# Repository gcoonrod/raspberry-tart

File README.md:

# raspberry-tart

 Raspberry Pi Pico Debug Hat for Pi 3/4

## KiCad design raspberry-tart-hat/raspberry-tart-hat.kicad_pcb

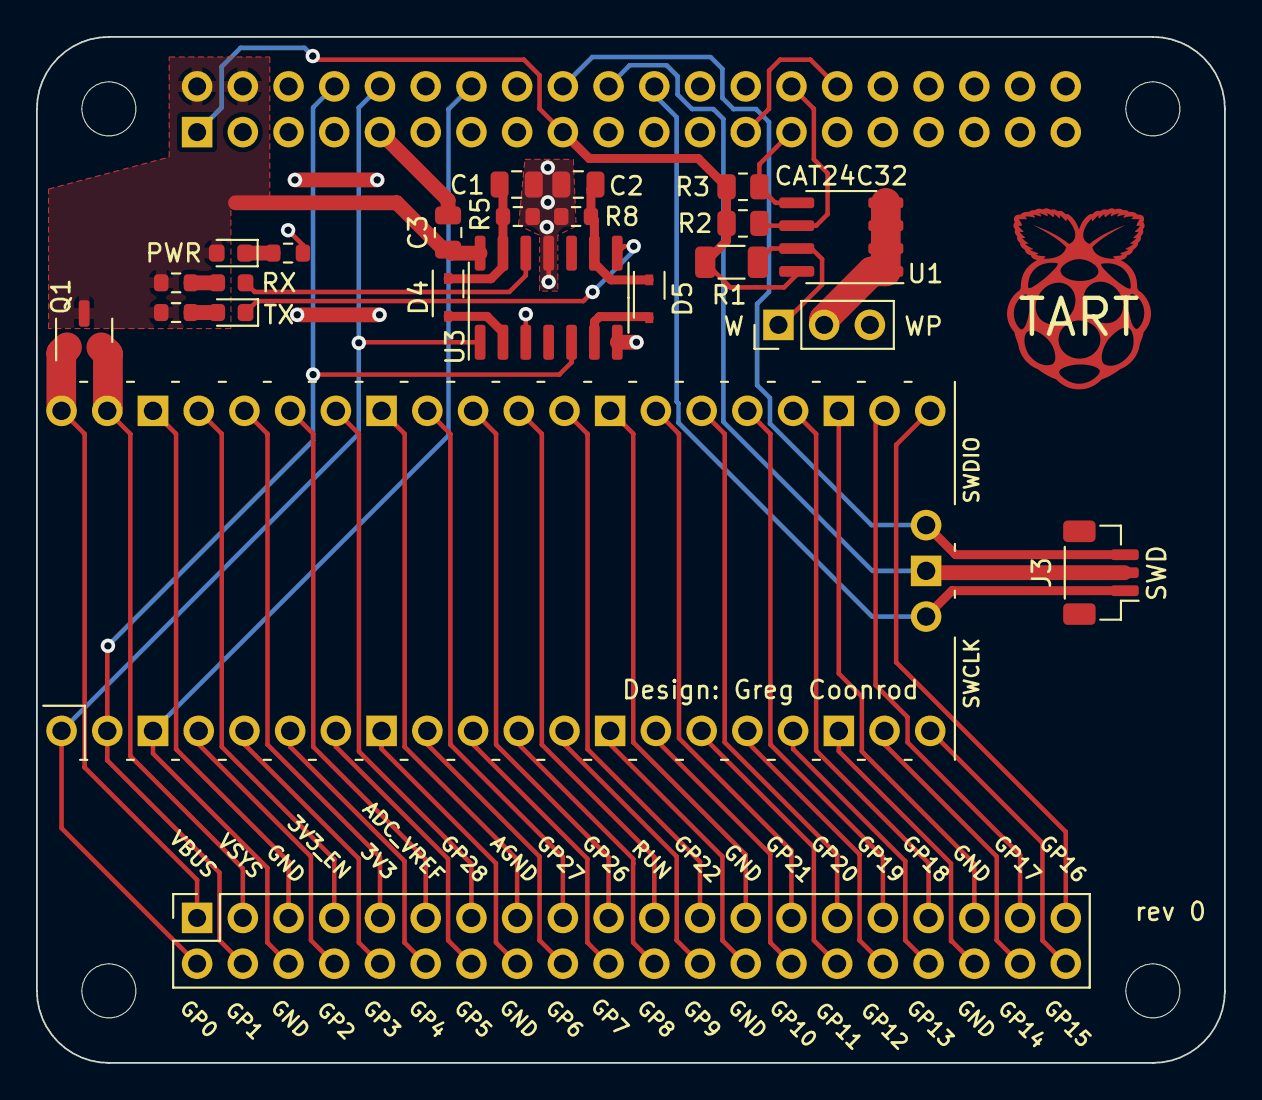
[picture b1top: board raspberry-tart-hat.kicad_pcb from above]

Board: 2 copper layers, 66.0 x 57.0 mm, 28 parts (1 on the bottom side), 52 nets.

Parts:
C1, C2: 10n; C_0805_2012Metric
C3: 100n; C_0805_2012Metric
D1: LED_PWR; LED_0603_1608Metric
D2: LED_RX; LED_0603_1608Metric
D3: LED_TX; LED_0603_1608Metric
D4, D5: 1N4148WS; D_SOD-323
H1, H2, H3, H4: 3mm; MountingHole_3mm
J1: 40HAT; PinSocket_2x20_P2.54mm_Vertical
J2: HDR_WP; PinHeader_1x03_P2.54mm_Vertical
J3: JST_SH_SWD; JST_SH_BM03B-SRSS-TB_1x03-1MP_P1.00mm_Vertical
J7: HDR_PICO; PinSocket_2x20_P2.54mm_Vertical
Q1: DMG2305UX; SOT-23
R1: 1k; R_1206_3216Metric
R2, R3: 3k9; R_0805_2012Metric
R4, R7, R9: 330; R_0603_1608Metric
R5, R8: 1M; R_0603_1608Metric
U1: CAT24C32; SOIC-8_3.9x4.9mm_P1.27mm
U2: Pico; RPi_Pico_SMD_TH
U3: 74HC14; SOIC-14_3.9x8.7mm_P1.27mm

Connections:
+3V3: J1.1 (P3V3), J1.17 (P3V3), R1.2, R2.1, R3.1, U1.8 (VCC)
+5V: C3.1, D1.2 (A), J1.2 (P5V), J1.4 (P5V), Q1.3 (D), R4.2, R7.2, U3.14 (VCC)
/3V3: J7.9, U2.36 (3V3)
/3V3_EN: J7.7, U2.37 (3V3_EN)
/ADC_VREF: J7.11, U2.35 (ADC_VREF)
/AGND: J7.15, U2.33 (AGND)
/GPIO2: J7.8, U2.4 (GPIO2)
/GPIO3: J7.10, U2.5 (GPIO3)
/GPIO4: J7.12, U2.6 (GPIO4)
/GPIO5: J7.14, U2.7 (GPIO5)
/GPIO6: J7.18, U2.9 (GPIO6)
/GPIO7: J7.20, U2.10 (GPIO7)
/GPIO8: J7.22, U2.11 (GPIO8)
/GPIO9: J7.24, U2.12 (GPIO9)
/GPIO10: J7.28, U2.14 (GPIO10)
/GPIO11: J7.30, U2.15 (GPIO11)
/GPIO12: J7.32, U2.16 (GPIO12)
/GPIO13: J7.34, U2.17 (GPIO13)
/GPIO14: J7.38, U2.19 (GPIO14)
/GPIO15: J7.40, U2.20 (GPIO15)
/GPIO16: J7.39, U2.21 (GPIO16)
/GPIO17: J7.37, U2.22 (GPIO17)
/GPIO18: J7.33, U2.24 (GPIO18)
/GPIO19: J7.31, U2.25 (GPIO19)
/GPIO20: J7.29, U2.26 (GPIO20)
/GPIO21: J7.27, U2.27 (GPIO21)
/GPIO22: J7.23, U2.29 (GPIO22)
/GPIO26: J7.19, U2.31 (GPIO26_ADC0)
/GPIO27: J7.17, U2.32 (GPIO27_ADC1)
/GPIO28: J7.13, U2.34 (GPIO28_ADC2)
/HAT/ID_SC: J1.28 (BCM1), R2.2, U1.6 (SCL)
/HAT/ID_SD: J1.27 (BCM0), R3.2, U1.5 (SDA)
/HAT/WP_PU: J2.1, R1.1, U1.7 (WP)
/RUN: J7.21, U2.30 (RUN)
/RXD_PI: J1.10 (BCM15), J7.2, U2.1 (GPIO0), U3.1
/SWCLK: J1.22 (BCM25), J3.1, U2.41 (SWCLK)
/SWDIO: J1.18 (BCM24), J3.3, U2.43 (SWDIO)
/SWD_GND: J1.20 (GND), J3.2, U2.42 (GND)
/TXD_PI: J1.8 (BCM14), J7.4, U2.2 (GPIO1), U3.5
/UART_GND: J1.14 (GND), J7.6, U2.3 (GND)
/VBUS: J7.1, Q1.1 (G), U2.40 (VBUS)
/VSYS: J7.3, Q1.2 (S), U2.39 (VSYS)
GND: C1.2, C2.2, C3.2, J1.6 (GND), J1.9 (GND), J1.25 (GND), J1.30 (GND), J1.34 (GND), J1.39 (GND), J2.2, J7.5, J7.16, J7.25, J7.26, J7.35, J7.36, R5.1, R8.1, R9.1, U1.1 (A0), U1.2 (A1), U1.3 (A2), U1.4 (GND), U2.8 (GND), U2.13 (GND), U2.18 (GND), U2.23 (GND), U2.28 (GND), U2.38 (GND), U3.3, U3.7 (GND), U3.11
unnamed: C1.1, D4.1 (K), R5.2, U3.13
unnamed: C2.1, D5.1 (K), R8.2, U3.9
unnamed: D1.1 (K), R9.2
unnamed: D2.1 (K), U3.12
unnamed: D2.2 (A), R4.1
unnamed: D3.1 (K), U3.8
unnamed: D3.2 (A), R7.1
unnamed: D4.2 (A), U3.2
unnamed: D5.2 (A), U3.6

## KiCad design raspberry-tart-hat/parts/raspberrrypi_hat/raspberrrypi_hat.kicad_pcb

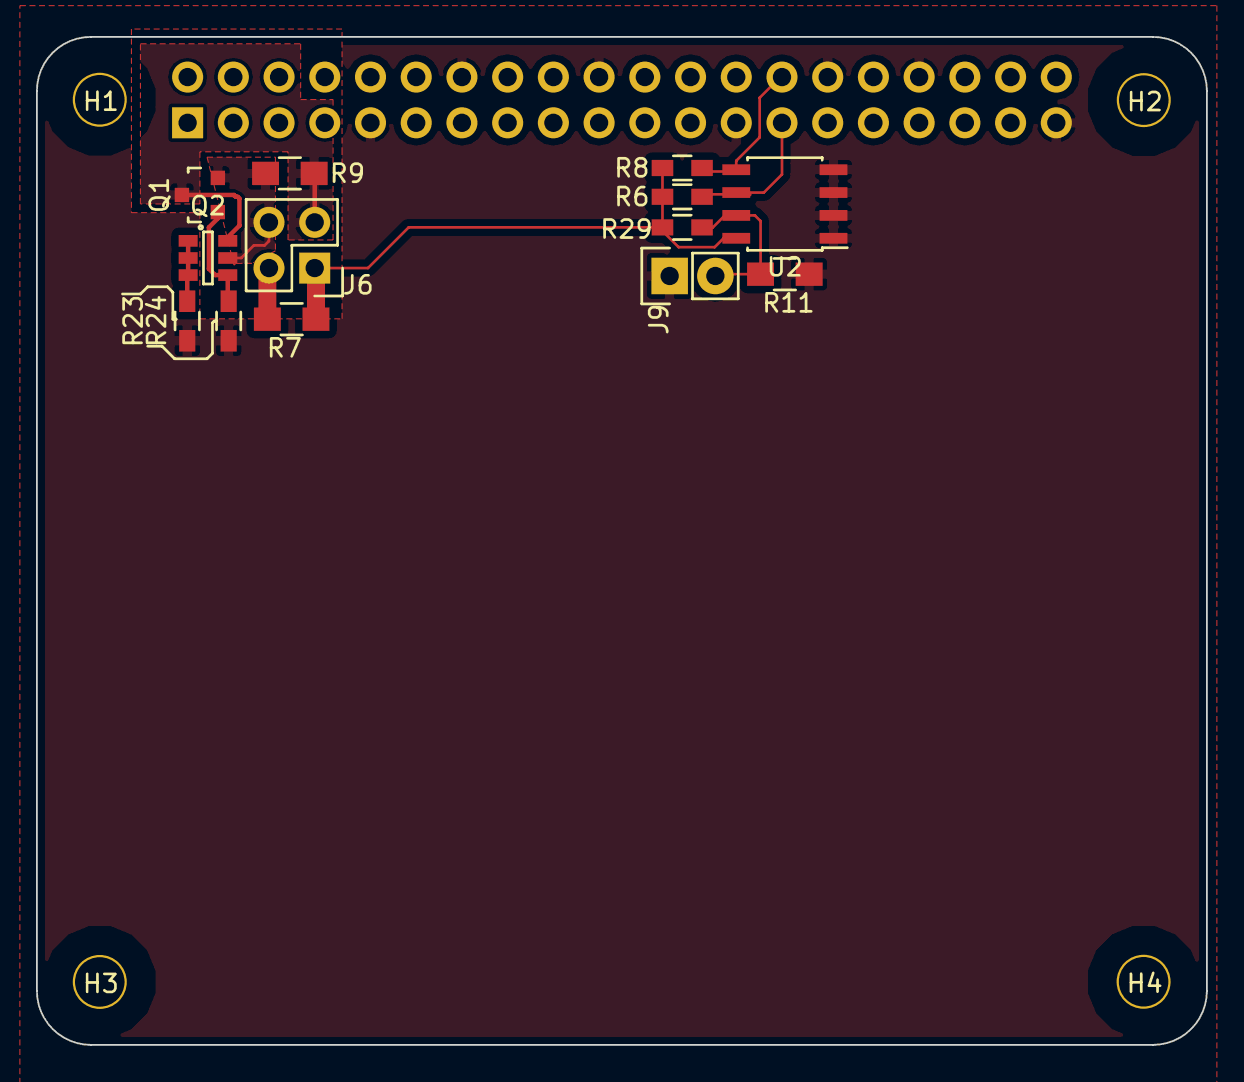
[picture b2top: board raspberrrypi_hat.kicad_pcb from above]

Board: 4 copper layers, 65.0 x 56.0 mm, 18 parts (1 on the bottom side), 10 nets.

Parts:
H1, H2, H3, H4: 3mm_Mounting_Hole; NPTH_3mm_ID
J3: 40HAT; Socket_Strip_Straight_2x20
J6: CONN_02X02; Pin_Header_Straight_2x02
J9: CONN_01X02; Pin_Header_Straight_1x02
Q1: DMG2305UX; SOT-23
Q2: DMMT5401; SOT-23-6
R6, R8: 3.9K; R_0603_HandSoldering
R7, R9, R11: DNP; R_0805_HandSoldering
R23, R24: 22; R_0603_HandSoldering
R29: 10K; R_0603_HandSoldering
U2: CAT24C32; SOIC-8_3.9x4.9mm_Pitch1.27mm

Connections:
/ID_SC_EEPROM: J3.28, R8.2, U2.5
/ID_SD_EEPROM: J3.27, R6.2, U2.6
/P3V3: J6.1, R6.1, R7.2, R8.1, R29.1, U2.8
/P3V3_HAT: J3.1, J6.2, R7.1
/P5V: J6.3, Q1.3, Q2.6, R9.2
/P5V_HAT: J3.2, J3.4, J6.4, Q1.2, Q2.5, R9.1
GND: J3.6, J3.9, J3.14, J3.20, J3.25, J3.30, J3.34, J3.39, J9.1, R11.2, R23.2, R24.2, U2.1, U2.2, U2.3, U2.4
unnamed: J9.2, R11.1, R29.2, U2.7
unnamed: Q1.1, Q2.4, R24.1
unnamed: Q2.1, Q2.2, Q2.3, R23.1

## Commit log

2023-02-13 initial project setup
2023-02-13 Update imported pi hat project
2023-02-13 Initial schematic complete.
2023-02-13 Initial pcb layout complete
